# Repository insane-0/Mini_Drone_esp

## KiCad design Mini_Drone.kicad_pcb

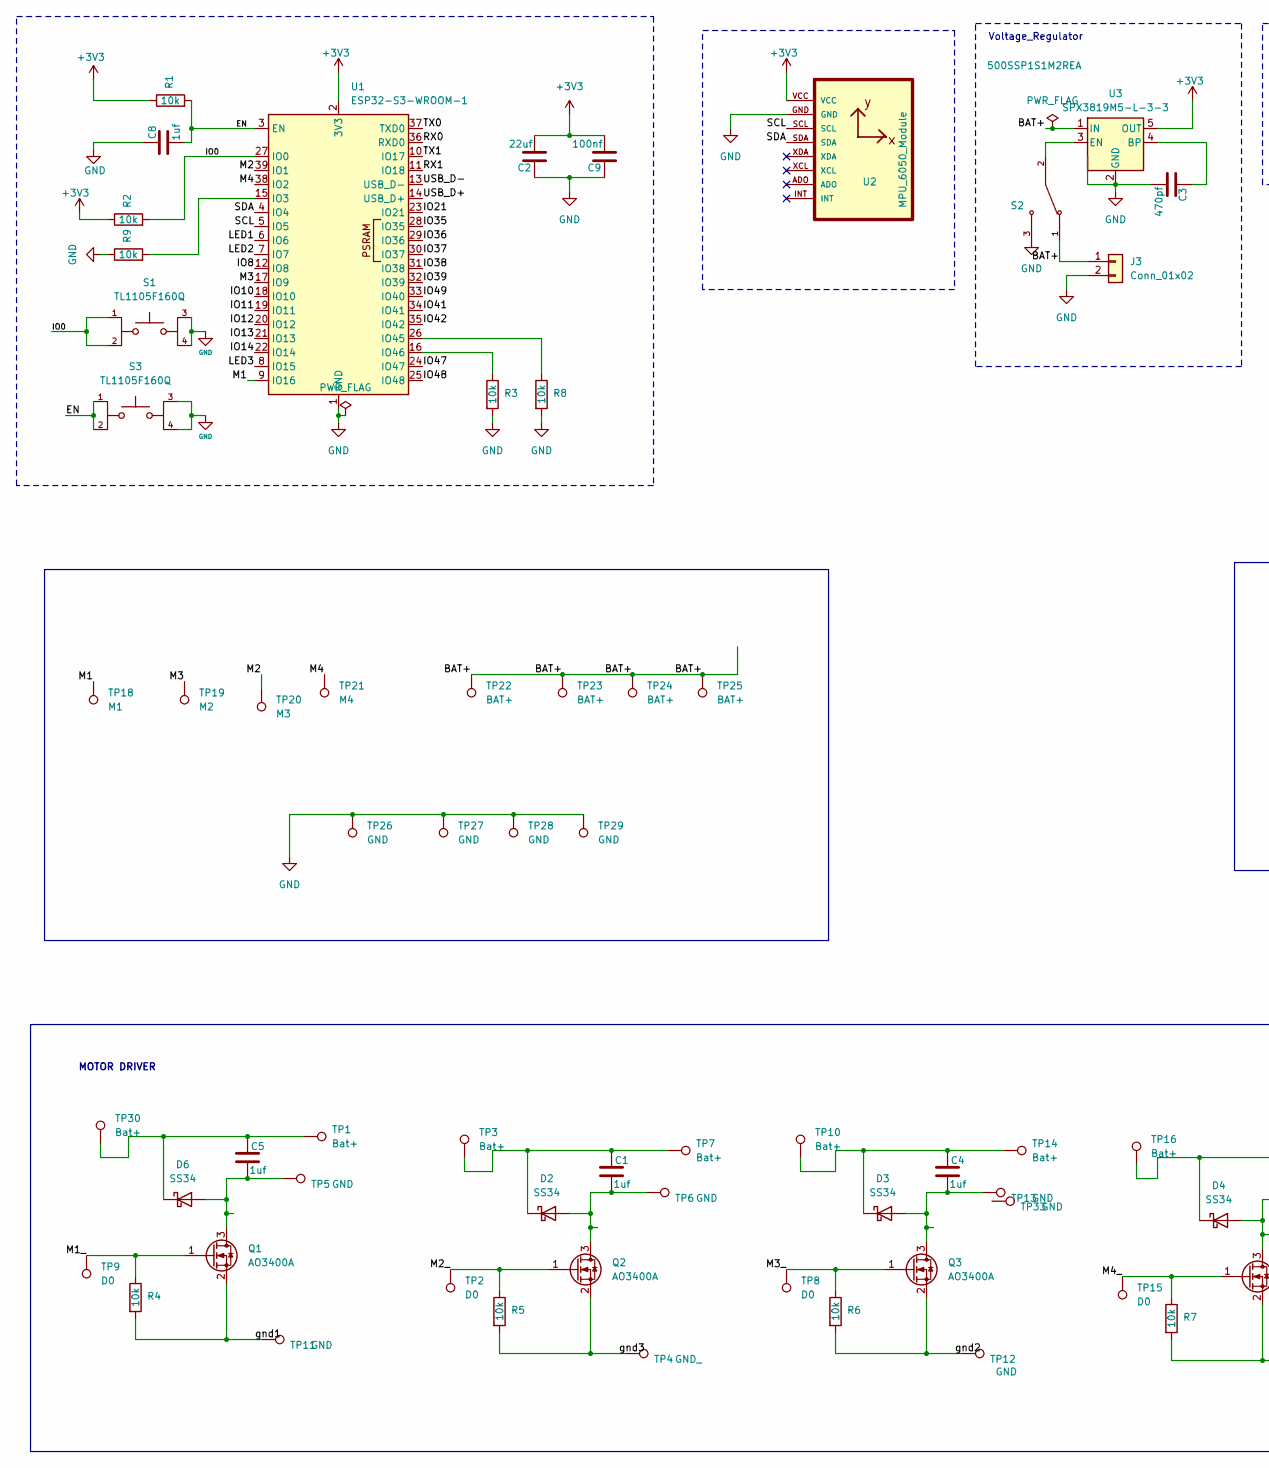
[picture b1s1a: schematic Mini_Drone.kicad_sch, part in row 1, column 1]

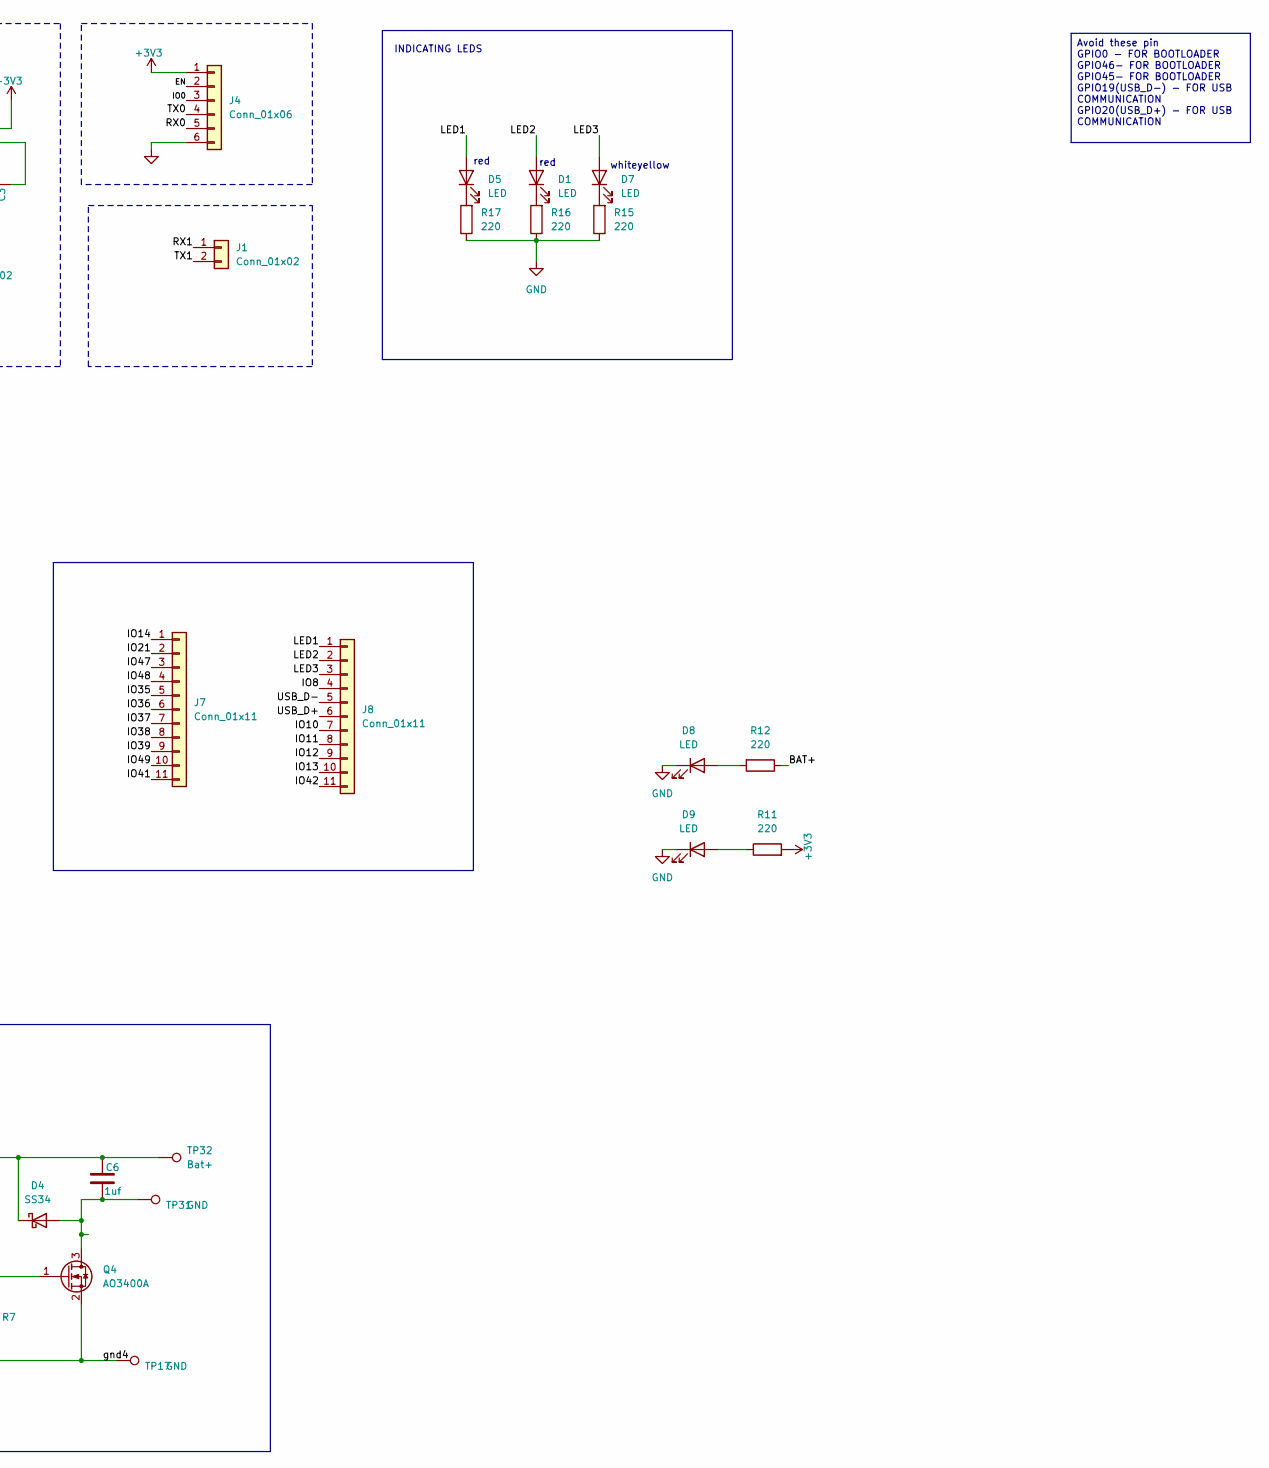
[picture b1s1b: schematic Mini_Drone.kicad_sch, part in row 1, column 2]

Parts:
C1, C4, C5, C6, C8: 1uf; C_0603_1608Metric; MFR.Part# CL10A105KB8NNNC; LCSC Part # C15849
C2: 22uf; C_0603_1608Metric; MFR.Part# CL10A226MQ8NRNC; LCSC Part # C59461
C3: 470pf; C_0603_1608Metric; MFR.Part# 0603B471K500NT; LCSC Part # C1620
C9: 100nf; C_0603_1608Metric; MFR.Part# CC0603KRX7R9BB104; LCSC Part # C14663
D1, D5, D8: LED; LED_0603_1608Metric; LCSC Part # C2286
D2, D3, D4, D6: SS34; D_SMA; MFR.Part# SS34; LCSC Part # C8678
D7, D9: LED; LED_0603_1608Metric; LCSC Part # C2290
J1: Conn_01x02; PinHeader_1x02_P2.54mm_Vertical
J3: Conn_01x02; JST_EH_B2B-EH-A_1x02_P2.50mm_Vertical; LCSC Part # C160262
J4: Conn_01x06; PinHeader_1x06_P2.54mm_Vertical
J7, J8: Conn_01x11; PinHeader_1x11_P2.54mm_Vertical
Q1, Q2, Q3, Q4: AO3400A; SOT-23; MFR.Part # AO3400A; LCSC Part # C20917
R1, R2, R3, R4, R5, R6, R7, R8, R9: 10k; R_0603_1608Metric; MFR.Part # 0603WAF1002T5E; LCSC Part # C25804
R11, R12, R15, R16, R17: 220; R_0603_1608Metric; LCSC Part # C22962
S1, S3: TL1105F160Q; SW_TL1105F160Q
S2: 500SSP1S1M2REA; slide swithc; LCSC Part # C92655
TP1, TP3, TP7, TP10, TP14, TP16, TP30, TP32: Bat+; TestPoint_THTPad_2.0x2.0mm_Drill1.0mm
TP2, TP8, TP9, TP15: D0; TestPoint_THTPad_2.0x2.0mm_Drill1.0mm
TP4: GND_; TestPoint_THTPad_2.0x2.0mm_Drill1.0mm
TP5, TP6, TP11, TP12, TP13, TP17, TP26, TP27, TP28, TP29, TP31, TP33: GND; TestPoint_THTPad_2.0x2.0mm_Drill1.0mm
TP18: M1; TestPoint_THTPad_2.0x2.0mm_Drill1.0mm
TP19: M2; TestPoint_THTPad_2.0x2.0mm_Drill1.0mm
TP20: M3; TestPoint_THTPad_2.0x2.0mm_Drill1.0mm
TP21: M4; TestPoint_THTPad_2.0x2.0mm_Drill1.0mm
TP22, TP23, TP24, TP25: BAT+; TestPoint_THTPad_2.0x2.0mm_Drill1.0mm
U1: ESP32-S3-WROOM-1
U2: MPU_6050_Module
U3: SPX3819M5-L-3-3; SOT-23-5; LCSC Part # C9055

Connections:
+3V3: C2.2, C9.2, J4.1, R1.1, R2.1, R11.2, U1.2 (3V3), U2.VCC, U3.5 (OUT)
/BAT+: J3.1, R12.1, S2.1, TP22.1, TP23.1, TP24.1, TP25.1, U3.1 (IN)
/EN: C8.2, J4.2, R1.2, S3.1, S3.2, U1.3 (EN)
/IO0: J4.3, R2.2, S1.1, S1.2, U1.27 (IO0)
/IO8: J8.4, U1.12 (IO8)
/IO10: J8.7, U1.18 (IO10)
/IO11: J8.8, U1.19 (IO11)
/IO12: J8.9, U1.20 (IO12)
/IO13: J8.10, U1.21 (IO13)
/IO14: J7.1, U1.22 (IO14)
/IO21: J7.2, U1.23 (IO21)
/IO35: J7.5, U1.28 (IO35)
/IO36: J7.6, U1.29 (IO36)
/IO37: J7.7, U1.30 (IO37)
/IO38: J7.8, U1.31 (IO38)
/IO39: J7.9, U1.32 (IO39)
/IO41: J7.11, U1.34 (IO41)
/IO42: J8.11, U1.35 (IO42)
/IO47: J7.3, U1.24 (IO47)
/IO48: J7.4, U1.25 (IO48)
/IO49: J7.10, U1.33 (IO40)
/LED1: D5.2 (A), J8.1, U1.6 (IO6)
/LED2: D1.2 (A), J8.2, U1.7 (IO7)
/LED3: D7.2 (A), J8.3, U1.8 (IO15)
/M1: TP18.1, U1.9 (IO16)
/M1_: Q1.1 (G), R4.1, TP9.1
/M2: TP20.1, U1.39 (IO1)
/M2_: Q2.1 (G), R5.1, TP2.1
/M3: TP19.1, U1.17 (IO9)
/M3_: Q3.1 (G), R6.1, TP8.1
/M4: TP21.1, U1.38 (IO2)
/M4_: Q4.1 (G), R7.1, TP15.1
/RX0: J4.5, U1.36 (RXD0)
/RX1: J1.1, U1.11 (IO18)
/SCL: U1.5 (IO5), U2.SCL
/SDA: U1.4 (IO4), U2.SDA
/TX0: J4.4, U1.37 (TXD0)
/TX1: J1.2, U1.10 (IO17)
/USB_D+: J8.6, U1.14 (USB_D+)
/USB_D-: J8.5, U1.13 (USB_D-)
/gnd1: Q1.2 (S), R4.2, TP11.1
/gnd2: Q3.2 (S), R6.2, TP12.1
/gnd3: Q2.2 (S), R5.2, TP4.1
/gnd4: Q4.2 (S), R7.2, TP17.1
GND: C2.1, C3.2, C8.1, C9.1, D8.1 (K), D9.1 (K), J3.2, J4.6, R3.2, R8.2, R9.1, R15.1, R16.1, R17.1, S1.3, S1.4, S2.3, S3.3, S3.4, TP26.1, TP27.1, TP28.1, TP29.1, U1.1 (GND), U1.40 (GND), U1.41 (GND), U2.GND, U3.2 (GND)
unnamed: D1.1 (K), R16.2
unnamed: C1.2, D2.2 (A), Q2.3 (D), TP6.1
unnamed: C1.1, D2.1 (K), TP3.1, TP7.1
unnamed: C4.2, D3.2 (A), Q3.3 (D), TP13.1
unnamed: C4.1, D3.1 (K), TP10.1, TP14.1
unnamed: C6.2, D4.2 (A), Q4.3 (D), TP31.1
unnamed: C6.1, D4.1 (K), TP16.1, TP32.1
unnamed: D5.1 (K), R17.2
unnamed: C5.2, D6.2 (A), Q1.3 (D), TP5.1
unnamed: C5.1, D6.1 (K), TP1.1, TP30.1
unnamed: D7.1 (K), R15.2
unnamed: D8.2 (A), R12.2
unnamed: D9.2 (A), R11.1
unnamed: R9.2, U1.15 (IO3)
unnamed: R8.1, U1.26 (IO45)
unnamed: R3.1, U1.16 (IO46)
unnamed: C3.1, U3.4 (BP)
unnamed: S2.2, U3.3 (EN)

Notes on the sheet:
red
INDICATING LEDS
MOTOR DRIVER
whiteyellow
Voltage_Regulator
Avoid these pin GPIO0 - FOR BOOTLOADER GPIO46- FOR BOOTLOADER GPIO45- FOR BOOTLOADER GPIO19(USB_D-) - FOR USB COMMUNICATION GPIO20(USB_D+) - FOR USB COMMUNICATION

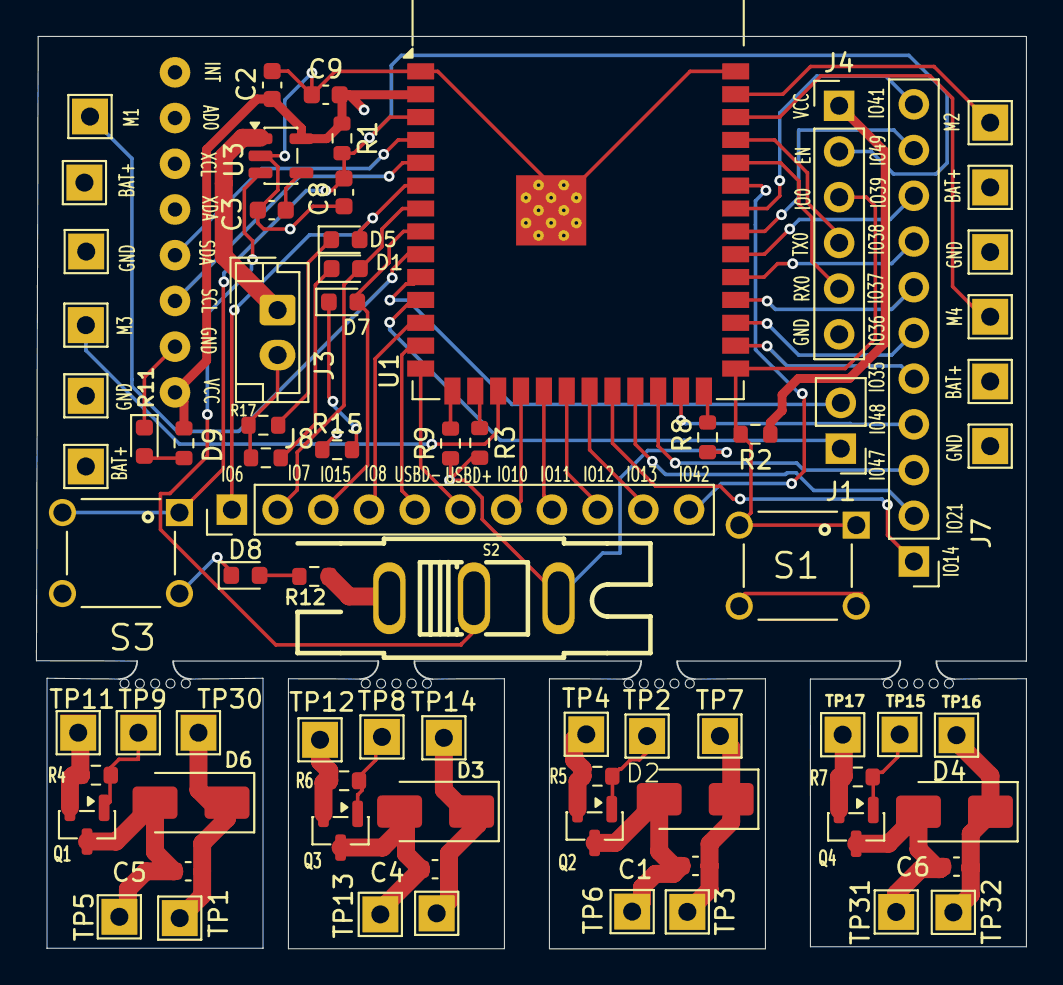
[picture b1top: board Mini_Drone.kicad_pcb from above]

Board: 4 copper layers, 54.9 x 50.6 mm, 78 parts (1 on the bottom side), 63 nets.

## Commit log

2025-11-21 sch completed need add net classes and route
2025-11-22 without motor driver silkscreen and neeed to make the routing a bit clearer and check the thickness
2025-11-23 add silkscreens and need to tidy up the routing and motor driver circuit is still there '
2025-11-23 main board completed need to tidy up the routing , motor driver yet to be completed
2025-11-23 motor driver circuit need to do the outline
2025-11-23 first prototype need to make the driver circuits symmetric and check everything assembly files yet to be made
2025-11-25 need to make it perfect change the switch and led outline needs to be corrected
2025-11-25 Hari's update
2025-11-26 error file not needed
2025-11-27 Almost finished need to check it before the ordering need check all the violaition
2025-11-28 need to add power indicating led and if possible add the switches
2025-11-30 Hari version switchled
2025-12-01 needs to increase the outline
2025-12-03 final checking and then order
2025-12-03 added gnd to the switch other terminal
2025-12-03 updated the production files
2025-12-03 rectified the unconnected gnd net need to again check everything before ordering once more
2026-01-07 switch connection has been corrected and the polygon pour has been reduced to one layer for gnd and the connection is set to thermaal relief for easier soldering
2026-01-22 smd pads has been changed to through hole pad and silkscreen has been arranged
